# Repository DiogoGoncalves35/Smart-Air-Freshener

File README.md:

# Smart Air Freshner

This board is designed to control a standard Air Freshener via ESPHome and Home Assistant, this way it's possible to automate the device by time or any condition defined.

The board fits in the same place as the default board because both have the same dimensions.

------------

### Schematic 

The [schematic](/Hardware/PCB/Schematic.pdf) is arround ESP12-E module with the basic configuration (Resistors needed), the AMS1117 regulates the 5V input voltage to 3.3V. The microcontroller controls the motor via an 2N2222 transistor and the 1N4007 diode protects the circuit in case of back voltage generated when the motor turns off.

------------

### PCB

[This](Hardware/PCB/) 1.6mm board contains 2 layers, both connected to GND, under the antenna GND area was removed. Programming connectors are SMD because it's only necessary to program the board once, after, it's possible to program over-the-air. Design it's not the best and should be improved, the only problem is related to component placement, there isn't much space to put the components on the edges.

---

### ESPHome Code

This code block contains the needed code to control the air freshener. Whenever Spray button is pressed in Home Assistant, the motor turns on for a second and then turns off. With the button inside HA, it's possible to automate the device in different ways.

```
button:
  - platform: template
    name: "Spray"
    icon: "mdi:air-purifier"
    on_press:
    - switch.turn_on: motor
    - delay: 1000ms
    - switch.turn_off: motor

switch:
  - platform: gpio
    pin: GPIO4
    id: motor
```
------------

### Known issues

- None for now

------------

### To-Do

- USB-C connector ? (Better for connecting, removes need for soldering)
- Fuse protection
- SMD components

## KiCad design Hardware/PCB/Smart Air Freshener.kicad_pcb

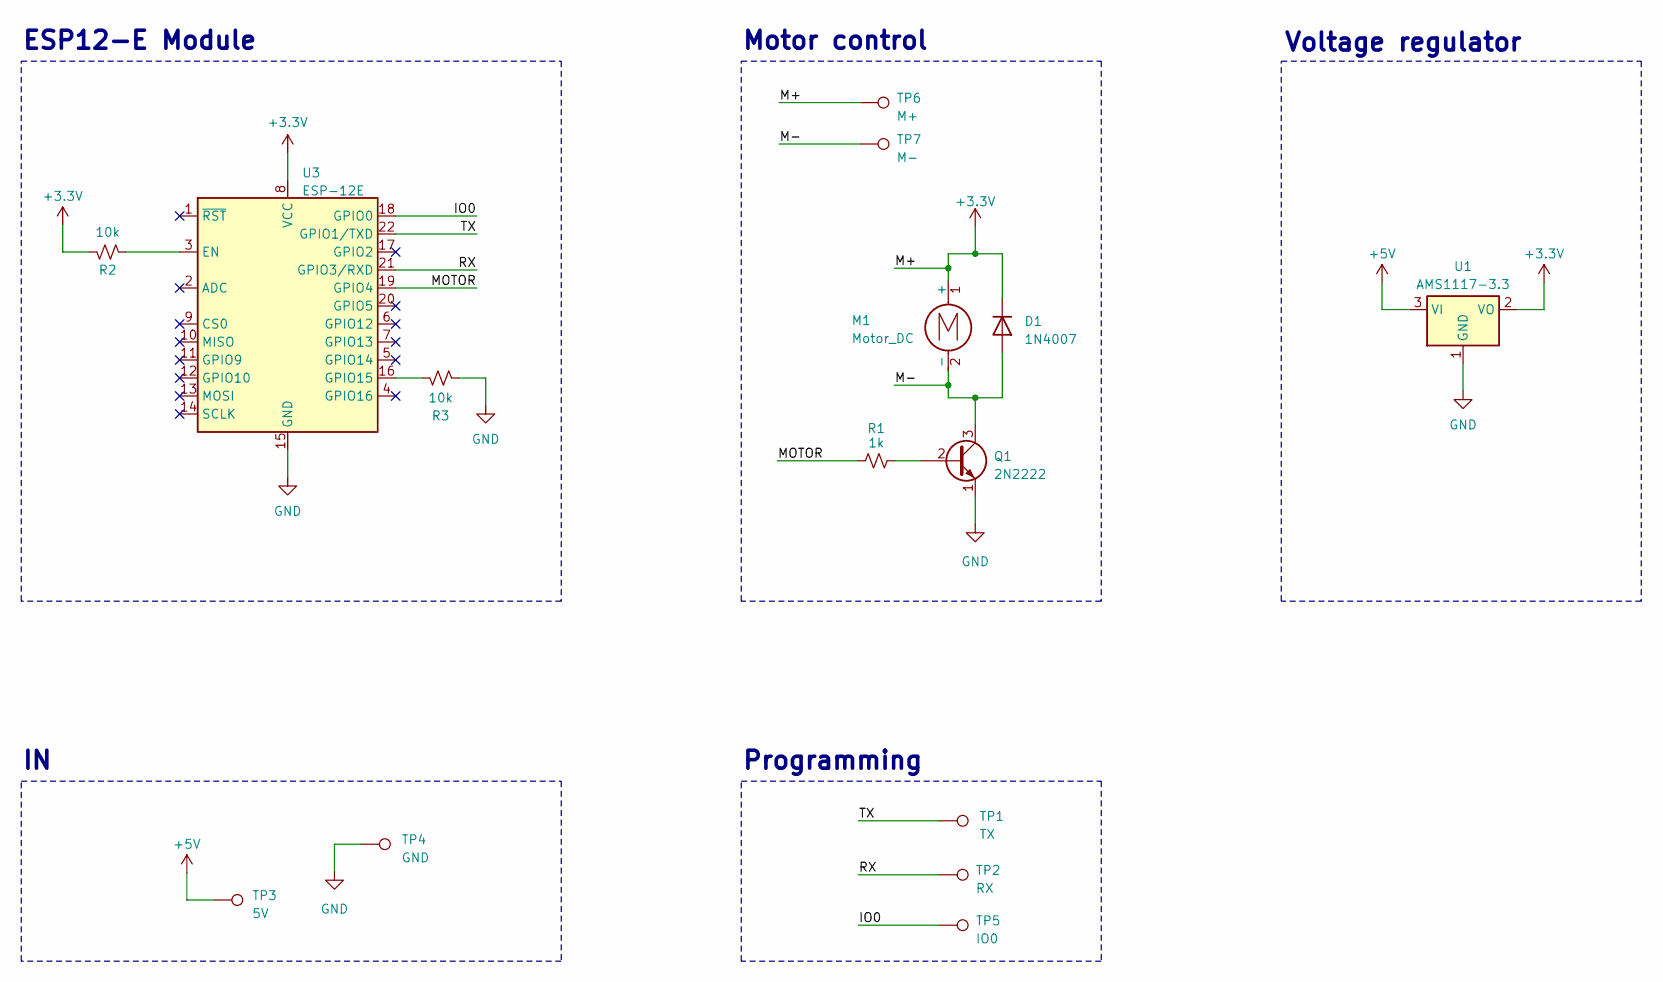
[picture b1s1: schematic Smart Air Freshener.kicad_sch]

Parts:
D1: 1N4007; D_DO-41_SOD81_P10.16mm_Horizontal
M1: Motor_DC
Q1: 2N2222; TO-92_HandSolder
R1: 1k; R_Axial_DIN0204_L3.6mm_D1.6mm_P2.54mm_Vertical
R2, R3: 10k; R_Axial_DIN0204_L3.6mm_D1.6mm_P2.54mm_Vertical; LCSC C25804
TP1: TX; TestPoint_Pad_1.0x1.0mm
TP2: RX; TestPoint_Pad_1.0x1.0mm
TP3: 5V; TestPoint_Pad_2.0x2.0mm
TP4: GND; TestPoint_Pad_2.0x2.0mm
TP5: IO0; TestPoint_Pad_1.0x1.0mm
TP6: M+; TestPoint_Pad_D3.0mm
TP7: M-; TestPoint_Pad_D3.0mm
U1: AMS1117-3.3; SOT-223-3_TabPin2
U3: ESP-12E

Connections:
+3.3V: D1.1 (K), M1.1 (+), R2.2, TP6.1, U1.2 (VO), U3.8 (VCC)
+5V: TP3.1, U1.3 (VI)
/IO0: TP5.1, U3.18 (GPIO0)
/M-: D1.2 (A), M1.2 (-), Q1.3 (C), TP7.1
/MOTOR: R1.1, U3.19 (GPIO4)
/RX: TP2.1, U3.21 (GPIO3/RXD)
/TX: TP1.1, U3.22 (GPIO1/TXD)
GND: Q1.1 (E), R3.2, TP4.1, U1.1 (GND), U3.15 (GND)
unnamed: Q1.2 (B), R1.2
unnamed: R2.1, U3.3 (EN)
unnamed: R3.1, U3.16 (GPIO15)

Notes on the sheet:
Voltage regulator
ESP12-E Module
Motor control
Programming

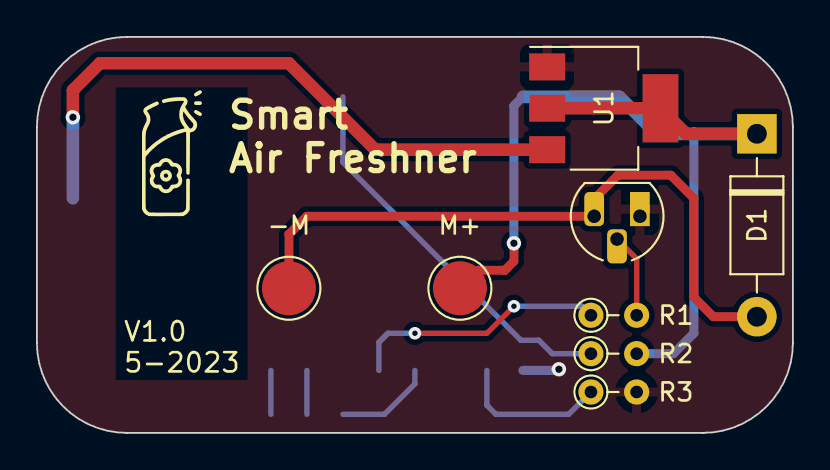
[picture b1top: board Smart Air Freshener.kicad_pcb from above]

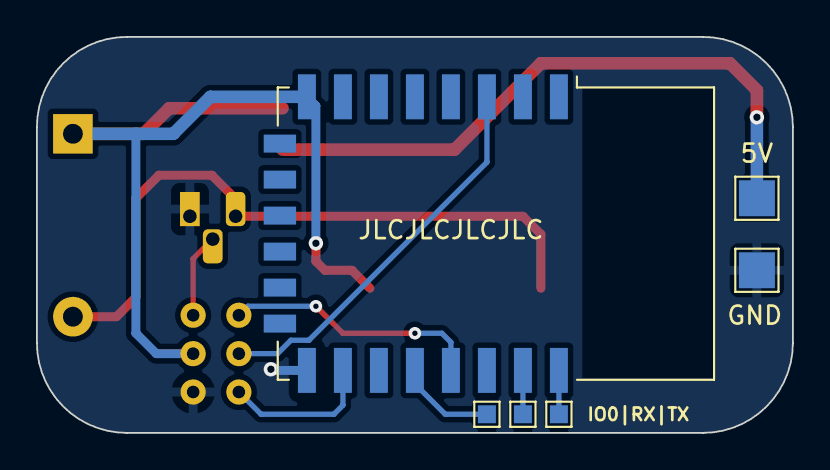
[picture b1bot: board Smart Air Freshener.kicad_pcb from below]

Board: 2 copper layers, 42.0 x 22.0 mm, 14 parts (6 on the bottom side), 11 nets.
